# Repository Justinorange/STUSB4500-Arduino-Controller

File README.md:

# STUSB4500 USB-C Power Delivery (PD) Sink Controller

A custom **KiCAD project** for building a **USB Power Delivery (USB-PD) Sink Board** utilizing the STMicroelectronics **STUSB4500** controller.

This board provides a powerful and flexible way to draw high-power **variable voltage** from any standard USB-C PD power source. It is designed to be fully controllable by an external host microcontroller, via the **I²C bus**.

---

## Features

* **USB-PD Protocol Negotiation**: Automatically handles the USB-PD handshake process.
* **I²C Control**: Allows a host MCU (e.g., Arduino, ESP32) to digitally request specific voltages.
* **Configurable Voltages**: Supports requesting standard USB-PD voltages: **5V, 9V, 12V, 15V, or 20V**.
* **Compact Design**: Designed as a simple, custom PCB project in KiCAD.

---

## Hardware Overview

The board is designed around the dedicated **STUSB4500** chip, which simplifies the PD sink implementation significantly by handling the communication protocol stack internally.

| Component | Description |
| :--- | :--- |
| **Controller IC** | STUSB4500 USB-PD Sink Controller |
| **Input** | USB-C receptacle for PD power source input |
| **Host Interface** | 5-pin JST connector for I²C communication with the microcontroller |
| **Power Output** | 2-pin JST connector for regulated DC output power |

The full schematic and PCB layout files are available in the KiCAD project directory (`/kicad/`).

---

## I²C Connection Pinout

This pinout is designed for compatibility with the ESP32 Arduino Nano, using a standard **5-pin JST header**.

| STUSB4500 Board Pin | Signal | Arduino (e.g., Nano/Uno) | Function |
| :--- | :--- | :--- | :--- |
| **SDA** | I²C Data | A4 | I²C Serial Data Line |
| **SCL** | I²C Clock | A5 | I²C Serial Clock Line |
| **RST** | Reset | D0 | External Reset Pin for STUSB4500 |
| **VDD** | Power Input | Vin (20V) | Power Supply for Arduino/STUSB4500 Logic |
| **GND** | Ground | GND | Common Ground Reference |

---

## How to Use (Arduino Example)

Follow these steps to quickly test and control the power negotiation using an Arduino or compatible microcontroller.

### Prerequisites

* **Code**: You will need the specific library/code to communicate with the STUSB4500 over I²C.
* **Connection**: Ensure the board is wired correctly according to the table above.
* **Power**: Connect a **USB-C PD power source** (charger) to the board's USB-C input.

### Negotiation Workflow

1.  **Upload**: Upload the I²C configuration code to your Arduino.
2.  **Monitor**: Open the **Serial Monitor** at 9600 baud.
3.  **Input**: Enter the desired target voltage (**5, 9, 12, 15, or 20**) and press Enter.
4.  **Negotiation**: The Arduino code will:
    * Configure the STUSB4500's I²C registers with the requested voltage.
    * The **STUSB4500 chip** will initiate a negotiation request to the power source.
5.  **Status**: The negotiated status (Success or Failure) and the resulting stable output voltage will be printed back to the Serial Monitor.
6.  **Output**: The requested voltage will be delivered to the **2-pin JST output terminal**.

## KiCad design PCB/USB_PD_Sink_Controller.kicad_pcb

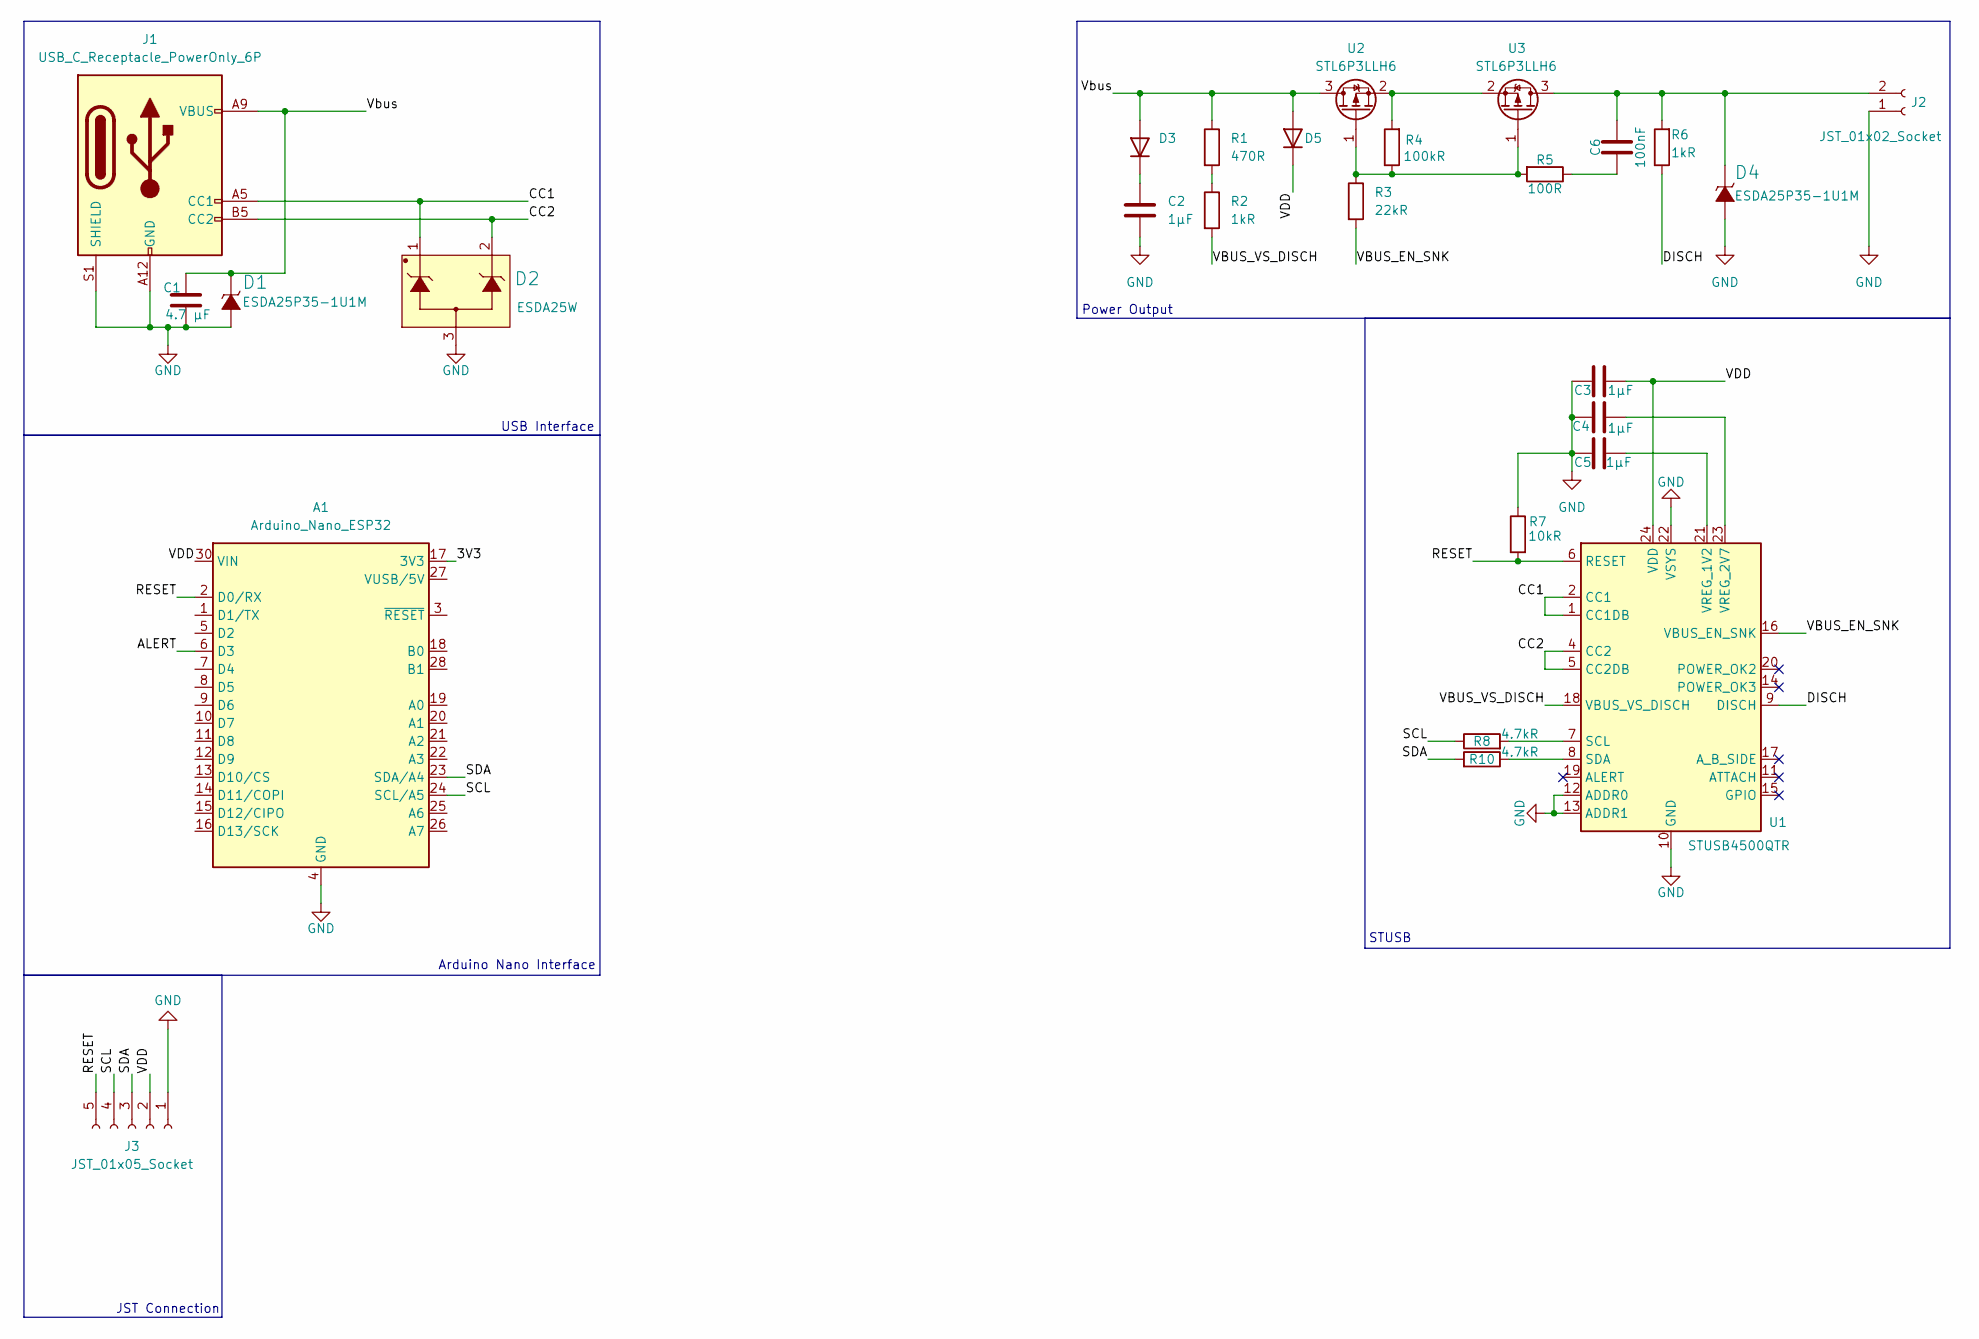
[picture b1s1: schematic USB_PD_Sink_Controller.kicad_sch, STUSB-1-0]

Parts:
A1: Arduino_Nano_ESP32; Arduino_Nano
C1: 4.7 μF; C_0603_1608Metric_Pad1.08x0.95mm_HandSolder
C2, C3, C4, C5: 1μF; C_0603_1608Metric_Pad1.08x0.95mm_HandSolder
C6: 100nF; C_0603_1608Metric_Pad1.08x0.95mm_HandSolder
D1, D4: ESDA25P35-1U1M; ST_1610
D2: ESDA25W; ST_SOT323-3L
D3, D5: D; D_0603_1608Metric_Pad1.05x0.95mm_HandSolder
J1: USB_C_Receptacle_PowerOnly_6P; USB_C_Receptacle_GCT_USB4105-xx-A_16P_TopMnt_Horizontal
J2: JST_01x02_Socket; JST_XH_S2B-XH-A_1x02_P2.50mm_Horizontal
J3: JST_01x05_Socket; JST_XH_S5B-XH-A_1x05_P2.50mm_Horizontal
R1: 470R; R_0603_1608Metric_Pad0.98x0.95mm_HandSolder
R2, R6: 1kR; R_0603_1608Metric_Pad0.98x0.95mm_HandSolder
R3: 22kR; R_0603_1608Metric_Pad0.98x0.95mm_HandSolder
R4: 100kR; R_0603_1608Metric_Pad0.98x0.95mm_HandSolder
R5: 100R; R_0603_1608Metric_Pad0.98x0.95mm_HandSolder
R7: 10kR; R_0603_1608Metric_Pad0.98x0.95mm_HandSolder
R8, R10: 4.7kR; R_0603_1608Metric_Pad0.98x0.95mm_HandSolder
U1: STUSB4500QTR; QFN-24-1EP_4x4mm_P0.5mm_EP2.7x2.7mm
U2, U3: STL6P3LLH6; POWERFLAT_3P3X3P3_STM2

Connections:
/CC1: D2.1, J1.A5 (CC1), U1.1 (CC1DB), U1.2 (CC1)
/CC2: D2.2, J1.B5 (CC2), U1.4 (CC2), U1.5 (CC2DB)
/DISCH: R6.1, U1.9 (DISCH)
/RESET: A1.2 (D0/RX), J3.5, R7.2, U1.6 (RESET)
/SCL: A1.24 (SCL/A5), J3.4, R8.1
/SDA: A1.23 (SDA/A4), J3.3, R10.2
/VBUS_EN_SNK: R3.2, U1.16 (VBUS_EN_SNK)
/VBUS_VS_DISCH: R2.2, U1.18 (VBUS_VS_DISCH)
/VDD: A1.30 (VIN), C3.1, D5.1 (K), J3.2, U1.24 (VDD)
/Vbus: C1.1, D1.1 (K), D3.2 (A), D5.2 (A), J1.A9 (VBUS), J1.B9 (VBUS), R1.1, U2.3 (D)
GND: A1.4 (GND), A1.29 (GND), C1.2, C2.2, C3.2, C4.2, C5.2, D1.2 (A), D2.3, D4.2 (A), J1.A12 (GND), J1.B12 (GND), J1.S1 (SHIELD), J2.1, J3.1, R7.1, U1.10 (GND), U1.12 (ADDR0), U1.13 (ADDR1), U1.22 (VSYS), U1.25 (GND)
unnamed: C6.1, R5.1
unnamed: C2.1, D3.1 (K)
unnamed: C6.2, D4.1 (K), J2.2, R6.2, U3.3 (D)
unnamed: R1.2, R2.1
unnamed: R8.2, U1.7 (SCL)
unnamed: R10.1, U1.8 (SDA)
unnamed: C5.1, U1.21 (VREG_1V2)
unnamed: C4.1, U1.23 (VREG_2V7)
unnamed: R3.1, R4.1, R5.2, U2.1 (G), U3.1 (G)
unnamed: R4.2, U2.2 (S), U3.2 (S)

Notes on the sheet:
STUSB
Arduino Nano Interface
JST Connection
USB Interface
Power Output

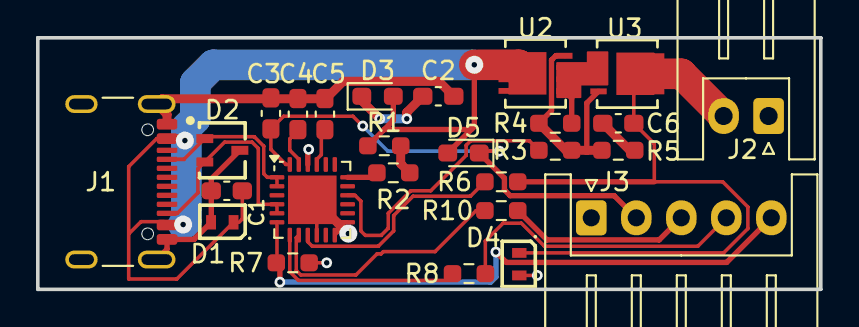
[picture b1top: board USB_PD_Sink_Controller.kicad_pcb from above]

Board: 2 copper layers, 43.5 x 14.0 mm, 26 parts (0 on the bottom side), 21 nets.

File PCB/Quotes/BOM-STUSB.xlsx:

BOM: STUSB-1-0
Assembly Part Number/Revision: 1
Item # | Quantity per board | Manufacturer Part # | Unit Price | Reference designators | Value (optional) | Total Price
2.0 | 1.0 | TMK107BBJ475KA-T | 0.28 | C1 | 4.7 μF | 0.28
3.0 | 4.0 | UMK107BJ105KA-T | 0.08 | C2,C3,C4,C5 | 1μF | 0.32
4.0 | 1.0 | TMK107BJ104KA-T | 0.08 | C6 | 100nF | 0.08
5.0 | 2.0 | ESDA25P35-1U1M | 0.37 | D1,D4 | ESDA25P35-1U1M | 0.74
6.0 | 1.0 | ESDA25W | 0.42 | D2 | ESDA25W | 0.42
7.0 | 2.0 | CD0603-B0240R | 0.21 | D3,D5 | Diode | 0.42
8.0 | 1.0 | USB4105-GF-A | 0.78 | J1 | USB_C_Receptacle_PowerOnly_6P | 0.78
9.0 | 1.0 | S2B-XH-A | 0.12 | J2 | JST_01x02_Socket | 0.12
10.0 | 1.0 | S5B-XH-A | 0.22 | J3 | JST_01x05_Socket | 0.22
11.0 | 1.0 | RC0603JR-07470RL | 0.1 | R1 | 470R | 0.1
12.0 | 2.0 | RT0603FRE071KL | 0.1 | R2,R6 | 1kR | 0.2
13.0 | 1.0 | RT0603DRE0722KL | 0.1 | R3 | 22kR | 0.1
14.0 | 1.0 | RC0603FR-07100KL | 0.1 | R4 | 100kR | 0.1
15.0 | 1.0 | RT0603DRE07100RL | 0.1 | R5 | 100R | 0.1
16.0 | 1.0 | CRCW080510K0FKEA | 0.1 | R7 | 10kR | 0.1
17.0 | 2.0 | RC0603JR-074K7L | 0.1 | R8,R10 | 4.7kR | 0.2
18.0 | 1.0 | STUSB4500QTR | 1.96 | U1 | STUSB4500QTR | 1.96
19.0 | 2.0 | STL6P3LLH6 | 1.54 | U2,U3 | STL6P3LLH6 | 3.08
Total | 9.32
END OF BOM

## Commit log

2025-09-10 Added KiCAD Files
2025-09-11 Added Pullup resistors and alert pin
2025-09-11 Update STUSB4500_Controller.ino
    Changed code to add alert pin
2025-09-11 Added capacitor to linear voltage regulator
2025-09-18 Revamped the PCB design
    Made many of the traces thicker. Changed from a barrel jack to a JST connector. Made the schematic pretty. Made the Arduino Nano directly soldered onto the board. Etc.
2025-09-25 Changed the code format to platformIO
2025-09-25 Update and rename USB_PD_Sink_Controller.kicad_pcb to PCB/USB_PD_Sink_Controller.kicad_pcb
    Moved File
2025-09-25 moved PCB files
2025-09-25 Added Ground plane and started LDO addition to SCH
2025-09-25 Added Arduino power explanation slides
2025-10-02 Made the Arduino esp32 and added a diode to prevent reverse voltage
2025-10-02 changed to ESP32 Arduino
2025-10-15 Added JST to schem
2025-10-16 VDD input added
2025-10-16 Updated PCB
2025-10-16 added Vbus variant
2025-10-16 added variant with less IO
2025-10-23 Made min VBUS main and added BOM
2025-10-23 Added price notes
2025-10-23 Changed file name
2025-10-23 cleanup on some files and PCB
2025-10-23 made small PCB change
2025-10-23 readme updated
